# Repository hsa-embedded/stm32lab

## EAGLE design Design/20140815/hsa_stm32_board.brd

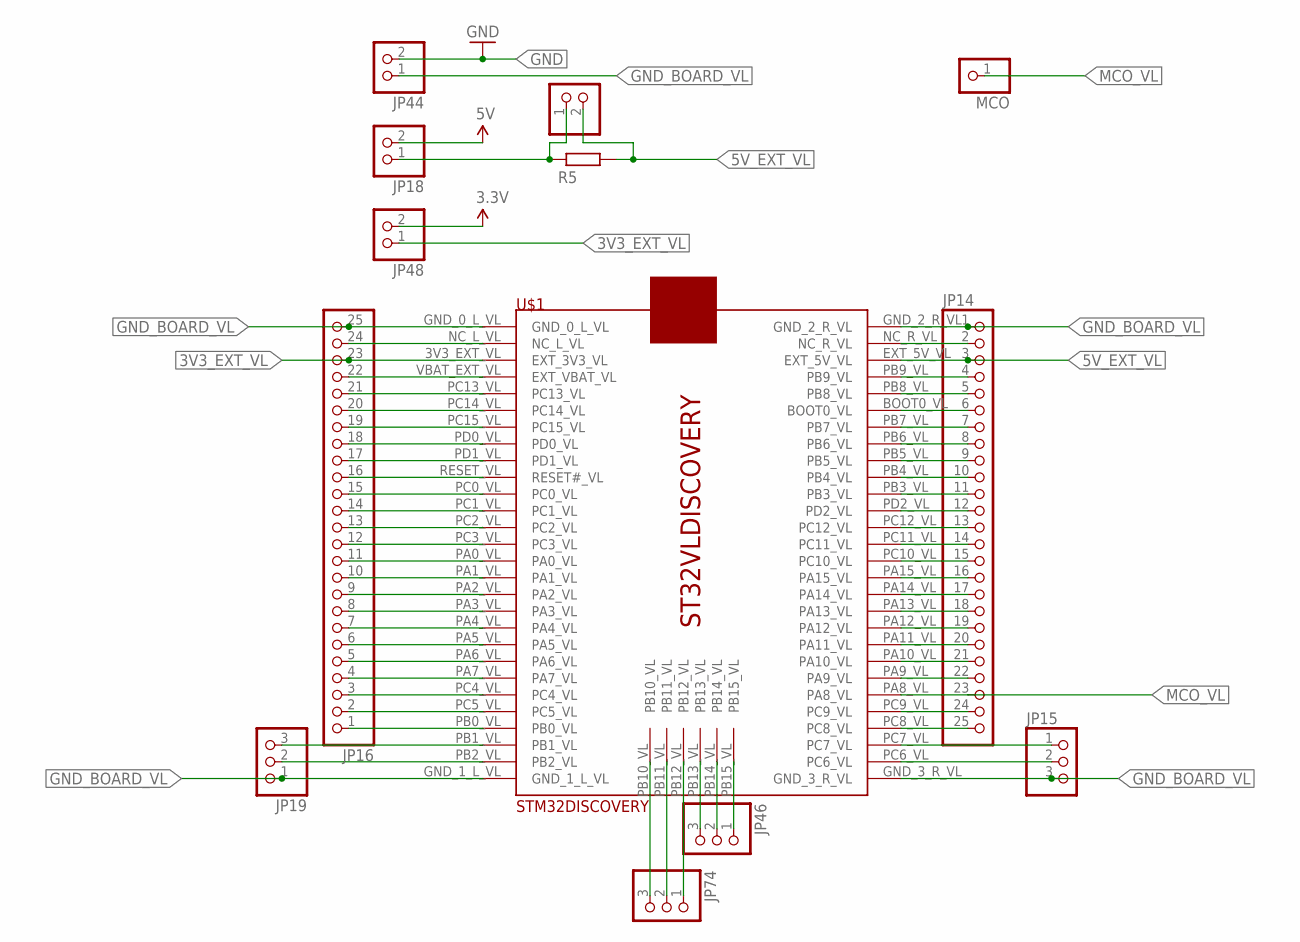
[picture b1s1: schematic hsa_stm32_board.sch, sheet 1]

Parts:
JP14, JP16: PINHD-1X25; 1X25
JP15, JP19, JP46, JP74: PINHD-1X3; 1X03
JP18, JP44, JP48, JP75: PINHD-1X2/90; 1X02/90
MCO: PINHD-1X1; 1X01
R5: R-EU_0207/10; 0207/10
U$1: STM32DISCOVERY

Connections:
3.3V: JP48.2; also elsewhere on the board
3V3_EXT_VL: JP16.23, JP48.1, U$1.3V3_EXT_VL (EXT_3V3_VL)
5V: JP18.2; also elsewhere on the board
5V_EXT_VL: JP14.3, JP75.2, R5.2, U$1.EXT_5V_VL
GND: JP44.2; also elsewhere on the board
GND_BOARD_VL: JP14.1, JP15.3, JP16.25, JP19.1, JP44.1, U$1.GND_0_L_VL, U$1.GND_1_L_VL, U$1.GND_2_R_VL, U$1.GND_3_R_VL
MCO_VL: JP14.23, MCO.1, U$1.PA8_VL
unnamed: JP18.1, JP75.1, R5.1
unnamed: JP14.2, U$1.NC_R_VL
unnamed: JP14.4, U$1.PB9_VL
unnamed: JP14.5, U$1.PB8_VL
unnamed: JP14.6, U$1.BOOT0_VL
unnamed: JP14.7, U$1.PB7_VL
unnamed: JP14.8, U$1.PB6_VL
unnamed: JP14.9, U$1.PB5_VL
unnamed: JP14.10, U$1.PB4_VL
unnamed: JP14.11, U$1.PB3_VL
unnamed: JP14.12, U$1.PD2_VL
unnamed: JP14.13, U$1.PC12_VL
unnamed: JP14.14, U$1.PC11_VL
unnamed: JP14.15, U$1.PC10_VL
unnamed: JP14.16, U$1.PA15_VL
unnamed: JP14.17, U$1.PA14_VL
unnamed: JP14.18, U$1.PA13_VL
unnamed: JP14.19, U$1.PA12_VL
unnamed: JP14.20, U$1.PA11_VL
unnamed: JP14.21, U$1.PA10_VL
unnamed: JP14.22, U$1.PA9_VL
unnamed: JP14.24, U$1.PC9_VL
unnamed: JP14.25, U$1.PC8_VL
unnamed: JP15.1, U$1.PC7_VL
unnamed: JP15.2, U$1.PC6_VL
unnamed: JP16.1, U$1.PB0_VL
unnamed: JP16.2, U$1.PC5_VL
unnamed: JP16.3, U$1.PC4_VL
unnamed: JP16.4, U$1.PA7_VL
unnamed: JP16.5, U$1.PA6_VL
unnamed: JP16.6, U$1.PA5_VL
unnamed: JP16.7, U$1.PA4_VL
unnamed: JP16.8, U$1.PA3_VL
unnamed: JP16.9, U$1.PA2_VL
unnamed: JP16.10, U$1.PA1_VL
unnamed: JP16.11, U$1.PA0_VL
unnamed: JP16.12, U$1.PC3_VL
unnamed: JP16.13, U$1.PC2_VL
unnamed: JP16.14, U$1.PC1_VL
unnamed: JP16.15, U$1.PC0_VL
unnamed: JP16.16, U$1.RESET_VL (RESET#_VL)
unnamed: JP16.17, U$1.PD1_VL
unnamed: JP16.18, U$1.PD0_VL
unnamed: JP16.19, U$1.PC15_VL
unnamed: JP16.20, U$1.PC14_VL
unnamed: JP16.21, U$1.PC13_VL
unnamed: JP16.22, U$1.VBAT_EXT_VL (EXT_VBAT_VL)
unnamed: JP16.24, U$1.NC_L_VL
unnamed: JP19.2, U$1.PB2_VL
unnamed: JP19.3, U$1.PB1_VL
unnamed: JP46.1, U$1.PB15_VL
unnamed: JP46.2, U$1.PB14_VL
unnamed: JP46.3, U$1.PB13_VL
unnamed: JP74.1, U$1.PB12_VL
unnamed: JP74.2, U$1.PB11_VL
unnamed: JP74.3, U$1.PB10_VL

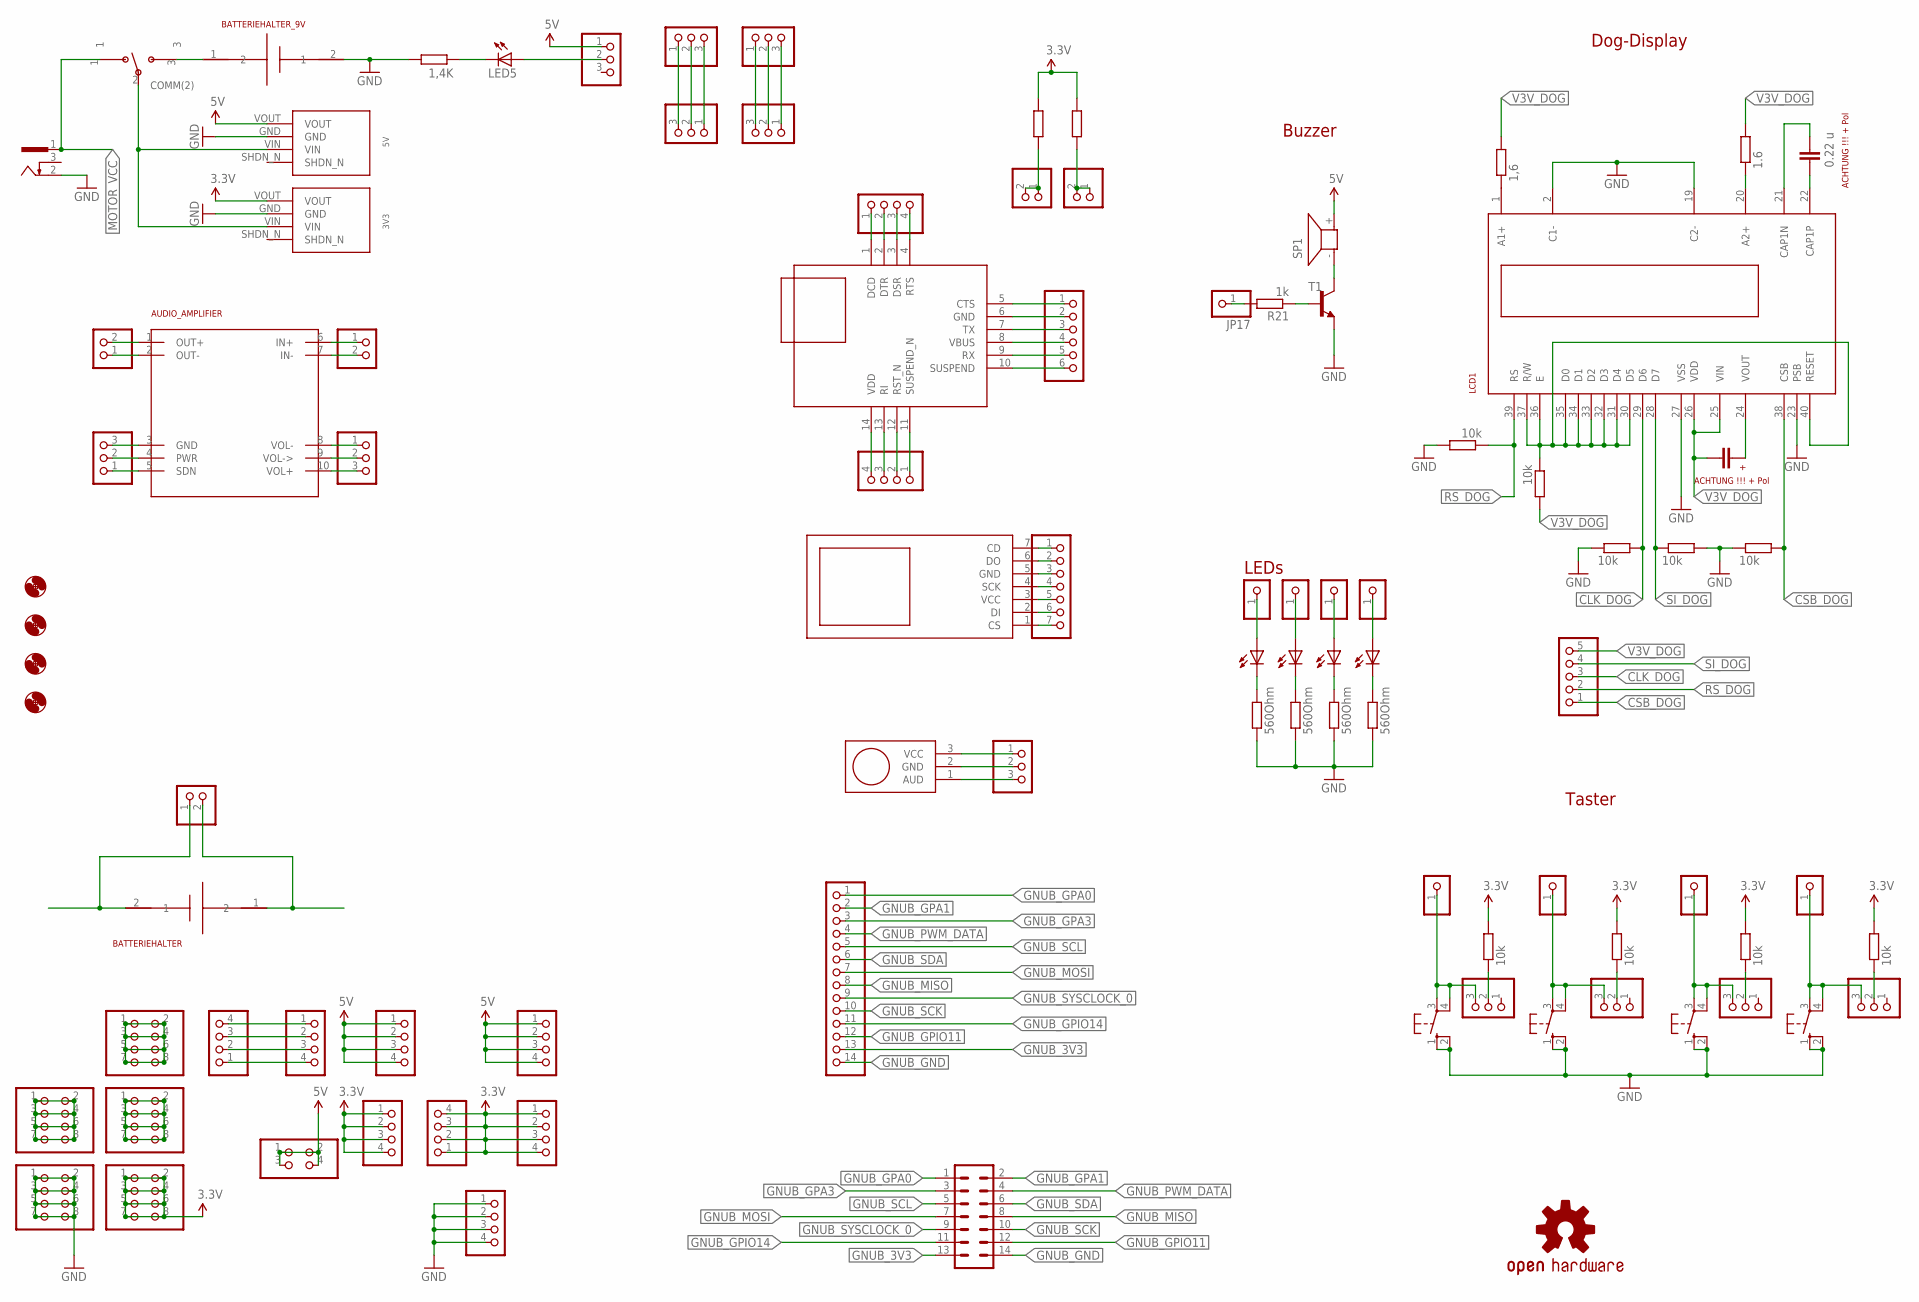
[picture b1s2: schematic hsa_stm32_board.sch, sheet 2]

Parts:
3V3, 5V: VOLTAGE_REGULATOR; VOL_REG
C2: 0.22 u; C025-040X050
C3: 1 u; C025-040X050
H1, H2, H3, H4: MOUNT-HOLE2.8; 2,8
JP1: PINHD-1X5; 1X05
JP4, JP30, JP33, JP34, JP50, JP52, JP59, JP60, JP61, JP62: PINHD-1X3; 1X03
JP5, JP6, JP7, JP8, JP9, JP10, JP11, JP12, JP17: PINHD-1X1; 1X01
JP24, JP28, JP29, JP36, JP37, JP40, JP41, JP42, JP47: PINHD-1X4; 1X04
JP27: PINHD-1X4/90; 1X04/90
JP31, JP32, JP43, JP65, JP66: PINHD-1X2; 1X02
JP38: PINHD-1X6; 1X06
JP39: PINHD-1X7; 1X07
JP45, JP67, JP68, JP69, JP70: PINHD-2X4; 2X04
JP49, JP51: PINHD-1X3/90; 1X03/90
JP64: PINHD-1X14; 1X14
JP71: PINHD-2X2; 2X02
LCD1: ZEITERFASSUNG_-OPTO_DOGM
LED1, LED2, LED3, LED4, LED5: LED5MM
LOGO1: OSHW-LOGOL; OSHW-LOGO-L
R1, R2, R3, R4: 560Ohm; 0207/10
R6: 1,4K; 0207/10
R7: 1.6; 0207/10
R8: 1,6; 0207/10
R9, R10, R11, R12, R13, R14, R15, R16, R17: 10k; 0207/10
R21: 1k; 0207/10
R22, R23: R-EU_0207/10; 0207/10
S1, S2, S3, S4: CPU-K_MODULE_REV3.0_SWITCH-OMRON_10-XX; CPU-K_MODULE_REV3.0_SWITCH-OMRON_B3F-10XX
SP1: BUZZER_F/PMX04; BUZZER_F/PMX04A
SV3: ML14
T1: TRANSISTOR_BC337; TRANSISTOR_TO92
U$2: USB_TO_SERIAL_ADAPTER; USB_TO_SERIAL
U$4: KIPPSCHALTER(EIN,AUS,EIN); KIPPSCHALTER
U$5: MIC
U$6: BATTERIEHALTER; BH_KZH_20
U$7: BATTERIEHALTER_9V
U$9: AUDIO_AMPLIFIER
U$12: MICRO_SD_HALTER; MIKRO_SD_HALTER
X1: 733980-62

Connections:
3.3V: 3V3.VOUT, JP29.1, JP29.2, JP29.3, JP29.4, JP41.1, JP41.2, JP41.3, JP41.4, JP47.1, JP47.2, JP47.3, JP47.4, JP70.1, JP70.2, JP70.3, JP70.4, JP70.5, JP70.6, JP70.7, JP70.8, R14.2, R15.2, R16.2, R17.2, R22.2, R23.2; also elsewhere on the board
5V: 5V.VOUT, JP4.1, JP28.1, JP28.2, JP28.3, JP28.4, JP40.1, JP40.2, JP40.3, JP40.4, JP71.1, JP71.2, JP71.3, JP71.4, SP1.+ (2); also elsewhere on the board
CLK_DOG: JP1.3, LCD1.29 (D6), R11.2
CSB_DOG: JP1.1, LCD1.38 (CSB), R13.2
GND: 3V3.GND, 5V.GND, JP42.1, JP42.2, JP42.3, JP42.4, JP67.1, JP67.2, JP67.3, JP67.4, JP67.5, JP67.6, JP67.7, JP67.8, LCD1.2 (C1-), LCD1.19 (C2-), LCD1.23 (PSB), LCD1.27 (VSS), R1.1, R2.1, R3.1, R4.1, R6.2, R9.2, R11.1, R12.2, R13.1, S1.1 (S), S1.2 (S1), S2.1 (S), S2.2 (S1), S3.1 (S), S3.2 (S1), S4.1 (S), S4.2 (S1), T1.1 (E), U$7.2 (1), X1.2; also elsewhere on the board
GNUB_3V3: JP64.13, SV3.13
GNUB_GND: JP64.14, SV3.14
GNUB_GPA0: JP64.1, SV3.1
GNUB_GPA1: JP64.2, SV3.2
GNUB_GPA3: JP64.3, SV3.3
GNUB_GPIO11: JP64.12, SV3.12
GNUB_GPIO14: JP64.11, SV3.11
GNUB_MISO: JP64.8, SV3.8
GNUB_MOSI: JP64.7, SV3.7
GNUB_PWM_DATA: JP64.4, SV3.4
GNUB_SCK: JP64.10, SV3.10
GNUB_SCL: JP64.5, SV3.5
GNUB_SDA: JP64.6, SV3.6
GNUB_SYSCLOCK_0: JP64.9, SV3.9
MOTOR_VCC: U$4.1, X1.1; also elsewhere on the board
unnamed: C2.2, LCD1.22 (CAP1P)
unnamed: C2.1, LCD1.21 (CAP1N)
unnamed: LCD1.20 (A2+), R7.1
unnamed: LCD1.30 (D5), LCD1.31 (D4), LCD1.32 (D3), LCD1.33 (D2), LCD1.34 (D1), LCD1.35 (D0), LCD1.36 (E), LCD1.37 (R/W), LCD1.40 (RESET), R10.1
unnamed: LCD1.1 (A1+), R8.1
unnamed: C3.2, LCD1.24 (VOUT)
unnamed: LED4.K (C), R4.2
unnamed: LED3.K (C), R3.2
unnamed: LED2.K (C), R2.2
unnamed: LED1.K (C), R1.2
unnamed: JP6.1, LED2.A
unnamed: JP7.1, LED3.A
unnamed: JP8.1, LED4.A
unnamed: 3V3.VIN, 5V.VIN, U$4.2 (COMM(2))
unnamed: JP62.2, R14.1
unnamed: JP61.2, R15.1
unnamed: JP9.1, JP62.3, S1.3, S1.4 (P1)
unnamed: JP10.1, JP61.3, S2.3, S2.4 (P1)
unnamed: JP60.2, R16.1
unnamed: JP59.2, R17.1
unnamed: JP11.1, JP60.3, S3.3, S3.4 (P1)
unnamed: JP12.1, JP59.3, S4.3, S4.4 (P1)
unnamed: U$4.3, U$7.1 (2)
unnamed: LED5.K (C), R6.1
unnamed: JP4.2, LED5.A
unnamed: JP5.1, LED1.A
unnamed: SP1.- (1), T1.3 (C)
unnamed: JP43.1, U$6.2 (1)
unnamed: JP17.1, R21.2
unnamed: JP43.2, U$6.1 (2)
unnamed: JP24.4, JP27.1
unnamed: JP24.3, JP27.2
unnamed: JP24.2, JP27.3
unnamed: JP24.1, JP27.4
unnamed: JP32.2, U$9.1 (OUT+)
unnamed: JP32.1, U$9.2 (OUT-)
unnamed: JP31.1, U$9.6 (IN+)
unnamed: JP31.2, U$9.7 (IN-)
unnamed: JP34.1, U$9.8 (VOL-)
unnamed: JP49.3, JP50.1
unnamed: JP49.2, JP50.2
unnamed: JP49.1, JP50.3
unnamed: JP30.1, U$5.3 (VCC)
unnamed: JP30.2, U$5.2 (GND)
unnamed: JP30.3, U$5.1 (AUD)
unnamed: JP34.2, U$9.9 (VOL->)
unnamed: JP34.3, U$9.10 (VOL+)
unnamed: JP33.3, U$9.3 (GND)
unnamed: JP33.2, U$9.4 (PWR)
unnamed: JP33.1, U$9.5 (SDN)
unnamed: JP36.1, U$2.1 (DCD)
unnamed: JP36.2, U$2.2 (DTR)
unnamed: JP36.3, U$2.3 (DSR)
unnamed: JP36.4, U$2.4 (RTS)
unnamed: JP37.1, U$2.11 (SUSPEND_N)
unnamed: JP37.2, U$2.12 (RST_N)
unnamed: JP37.3, U$2.13 (RI)
unnamed: JP37.4, U$2.14 (VDD)
unnamed: JP38.1, U$2.5 (CTS)
unnamed: JP38.2, U$2.6 (GND)
unnamed: JP38.3, U$2.7 (TX)
unnamed: JP38.4, U$2.8 (VBUS)
unnamed: JP38.5, U$2.9 (RX)
unnamed: JP38.6, U$2.10 (SUSPEND)
unnamed: JP39.1, U$12.7 (CD)
unnamed: JP39.2, U$12.6 (DO)
unnamed: JP39.3, U$12.5 (GND)
unnamed: JP39.4, U$12.4 (SCK)
unnamed: JP39.5, U$12.3 (VCC)
unnamed: JP39.6, U$12.2 (DI)
unnamed: JP39.7, U$12.1 (CS)
unnamed: JP51.3, JP52.1
unnamed: JP51.2, JP52.2
unnamed: JP51.1, JP52.3
unnamed: R21.1, T1.2 (B)
unnamed: JP65.1, JP65.2, R23.1
unnamed: JP66.1, JP66.2, R22.1
unnamed: JP45.1, JP45.2, JP45.3, JP45.4, JP45.5, JP45.6, JP45.7, JP45.8
unnamed: JP68.1, JP68.2, JP68.3, JP68.4, JP68.5, JP68.6, JP68.7, JP68.8
unnamed: JP69.1, JP69.2, JP69.3, JP69.4, JP69.5, JP69.6, JP69.7, JP69.8
RS_DOG: JP1.2, LCD1.39 (RS), R9.1
SI_DOG: JP1.4, LCD1.28 (D7), R12.1
V3V_DOG: C3.1, JP1.5, LCD1.25 (VIN), LCD1.26 (VDD), R7.2, R8.2, R10.2

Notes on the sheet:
Dog-Display
Taster
Buzzer
LEDs
ACHTUNG !!! + Pol

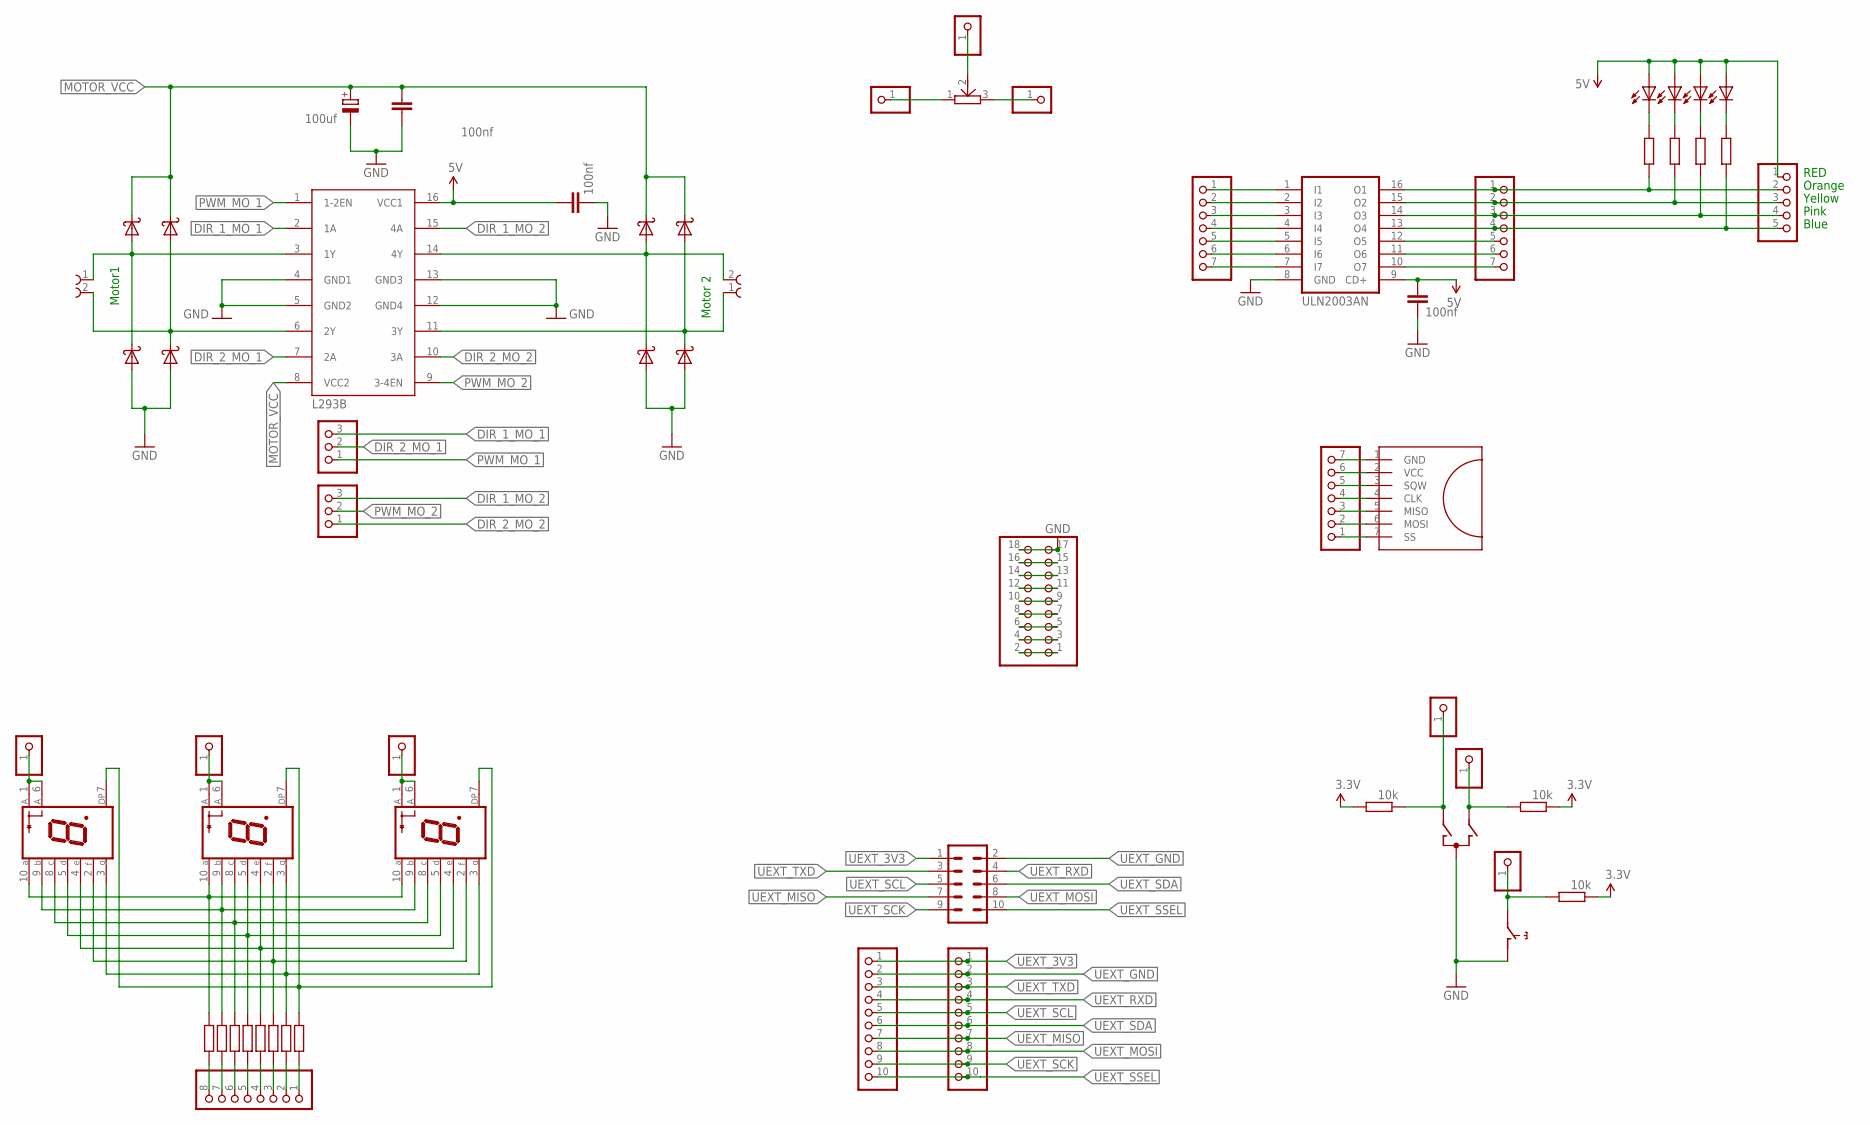
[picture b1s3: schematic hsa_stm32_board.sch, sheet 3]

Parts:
C4, C5, C6: 100nf; RCL_C025-040X050
C7: 100uf; RCL_E2,5-6
D1, D2, D3, D4, D5, D6, D7, D8: 1N5819; DO41-10
IC1: ULN2003AN; DIL16
IC2: L293D; DIL16
JP2, JP3, JP13, JP23, JP53, JP54, JP55, JP72, JP73: PINHD-1X1; 1X01
JP20, JP63: PINHD-1X10; 1X10
JP21, JP26, JP35: PINHD-1X7; 1X07
JP22: PINHD-1X8; 1X08
JP25: PINHD-1X5/90; 1X05/90
JP56: PINHD-2X9; 2X09
JP57, JP58: PINHD-1X3; 1X03
K1, K2: 691210910002
LED6, LED7, LED8: LA-401MD; LA-401
LED9, LED10, LED11, LED12: LED3MM
R18, R19, R20: 10k; 0207/10
R24, R25, R26, R27, R28, R29, R30, R31, R32, R33, R34, R35: R-EU_0207/10; 0207/10
SV2: CON-HARTING-ML_ML10
SW1: EC12E_SW; ALPS_EC12E_SW
U$10: RTC
U$17: THUMBWHEEL_POTI

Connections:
3.3V: R18.1, R19.2, R20.1; also elsewhere on the board
5V: C4.1, C6.1, IC1.9 (CD+), IC2.16 (VCC1), JP25.1, LED9.A, LED10.A, LED11.A, LED12.A; also elsewhere on the board
DIR_1_MO_1: IC2.2 (1A), JP57.3
DIR_1_MO_2: IC2.15 (4A), JP58.3
DIR_2_MO_1: IC2.7 (2A), JP57.2
DIR_2_MO_2: IC2.10 (3A), JP58.1
GND: C4.2, C5.2, C6.2, C7.-, D3.A, D4.A, D7.A, D8.A, IC1.8 (GND), IC2.4 (GND1), IC2.5 (GND2), IC2.12 (GND4), IC2.13 (GND3), JP56.17, JP56.18, SW1.C, SW1.D (1); also elsewhere on the board
MOTOR_VCC: C5.1, C7.+, D1.C, D2.C, D5.C, D6.C, IC2.8 (VCC2); also elsewhere on the board
unnamed: JP2.1, R19.1, SW1.A
unnamed: LED9.K (C), R32.2
unnamed: LED10.K (C), R34.2
unnamed: JP3.1, R18.2, SW1.B
unnamed: JP13.1, R20.2, SW1.E (2)
unnamed: D2.A, D4.C, IC2.14 (4Y), K1.2
unnamed: IC1.12 (O5), JP21.5
unnamed: IC1.11 (O6), JP21.6
unnamed: IC1.10 (O7), JP21.7
unnamed: IC1.5 (I5), JP26.5
unnamed: IC1.16 (O1), JP21.1, JP25.2, R32.1
unnamed: IC1.15 (O2), JP21.2, JP25.3, R34.1
unnamed: IC1.6 (I6), JP26.6
unnamed: IC1.7 (I7), JP26.7
unnamed: JP56.1, JP56.2
unnamed: JP56.3, JP56.4
unnamed: IC1.14 (O3), JP21.3, JP25.4, R33.1
unnamed: IC1.13 (O4), JP21.4, JP25.5, R35.1
unnamed: JP56.5, JP56.6
unnamed: IC1.4 (I4), JP26.4
unnamed: IC1.3 (I3), JP26.3
unnamed: IC1.2 (I2), JP26.2
unnamed: IC1.1 (I1), JP26.1
unnamed: JP56.7, JP56.8
unnamed: JP56.9, JP56.10
unnamed: JP56.11, JP56.12
unnamed: JP35.1, U$10.7 (SS)
unnamed: JP35.2, U$10.6 (MOSI)
unnamed: JP35.3, U$10.5 (MISO)
unnamed: JP35.4, U$10.4 (CLK)
unnamed: JP35.5, U$10.3 (SQW)
unnamed: JP35.6, U$10.2 (VCC)
unnamed: JP35.7, U$10.1 (GND)
unnamed: D1.A, D3.C, IC2.11 (3Y), K1.1
unnamed: JP55.1, U$17.1 (A)
unnamed: JP54.1, U$17.2 (W)
unnamed: D6.A, D8.C, IC2.3 (1Y), K2.1
unnamed: D5.A, D7.C, IC2.6 (2Y), K2.2
unnamed: JP53.1, U$17.3 (B)
unnamed: LED12.K (C), R35.2
unnamed: LED11.K (C), R33.2
unnamed: JP56.13, JP56.14
unnamed: JP56.15, JP56.16
unnamed: JP22.8, R24.1
unnamed: LED6.9 (B), LED7.9 (B), LED8.9 (B), R25.2
unnamed: LED6.8 (C), LED7.8 (C), LED8.8 (C), R26.2
unnamed: LED6.5 (D), LED7.5 (D), LED8.5 (D), R27.2
unnamed: LED6.4 (E), LED7.4 (E), LED8.4 (E), R28.2
unnamed: LED6.2 (F), LED7.2 (F), LED8.2 (F), R29.2
unnamed: LED6.3 (G), LED7.3 (G), LED8.3 (G), R30.2
unnamed: LED6.7 (DP), LED7.7 (DP), LED8.7 (DP), R31.2
unnamed: LED6.10 (A), LED7.10 (A), LED8.10 (A), R24.2
unnamed: JP22.7, R25.1
unnamed: JP22.6, R26.1
unnamed: JP22.5, R27.1
unnamed: JP22.4, R28.1
unnamed: JP22.3, R29.1
unnamed: JP22.2, R30.1
unnamed: JP22.1, R31.1
unnamed: JP72.1, LED6.1 (A), LED6.6 (A)
unnamed: JP73.1, LED7.1 (A), LED7.6 (A)
unnamed: JP23.1, LED8.1 (A), LED8.6 (A)
PWM_MO_1: IC2.1 (1-2EN), JP57.1
PWM_MO_2: IC2.9 (3-4EN), JP58.2
UEXT_3V3: JP20.1, JP63.1, SV2.1
UEXT_GND: JP20.2, JP63.2, SV2.2
UEXT_MISO: JP20.7, JP63.7, SV2.7
UEXT_MOSI: JP20.8, JP63.8, SV2.8
UEXT_RXD: JP20.4, JP63.4, SV2.4
UEXT_SCK: JP20.9, JP63.9, SV2.9
UEXT_SCL: JP20.5, JP63.5, SV2.5
UEXT_SDA: JP20.6, JP63.6, SV2.6
UEXT_SSEL: JP20.10, JP63.10, SV2.10
UEXT_TXD: JP20.3, JP63.3, SV2.3

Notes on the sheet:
L293B
Motor 2
Motor1
RED
Orange
Yellow
Pink
Blue

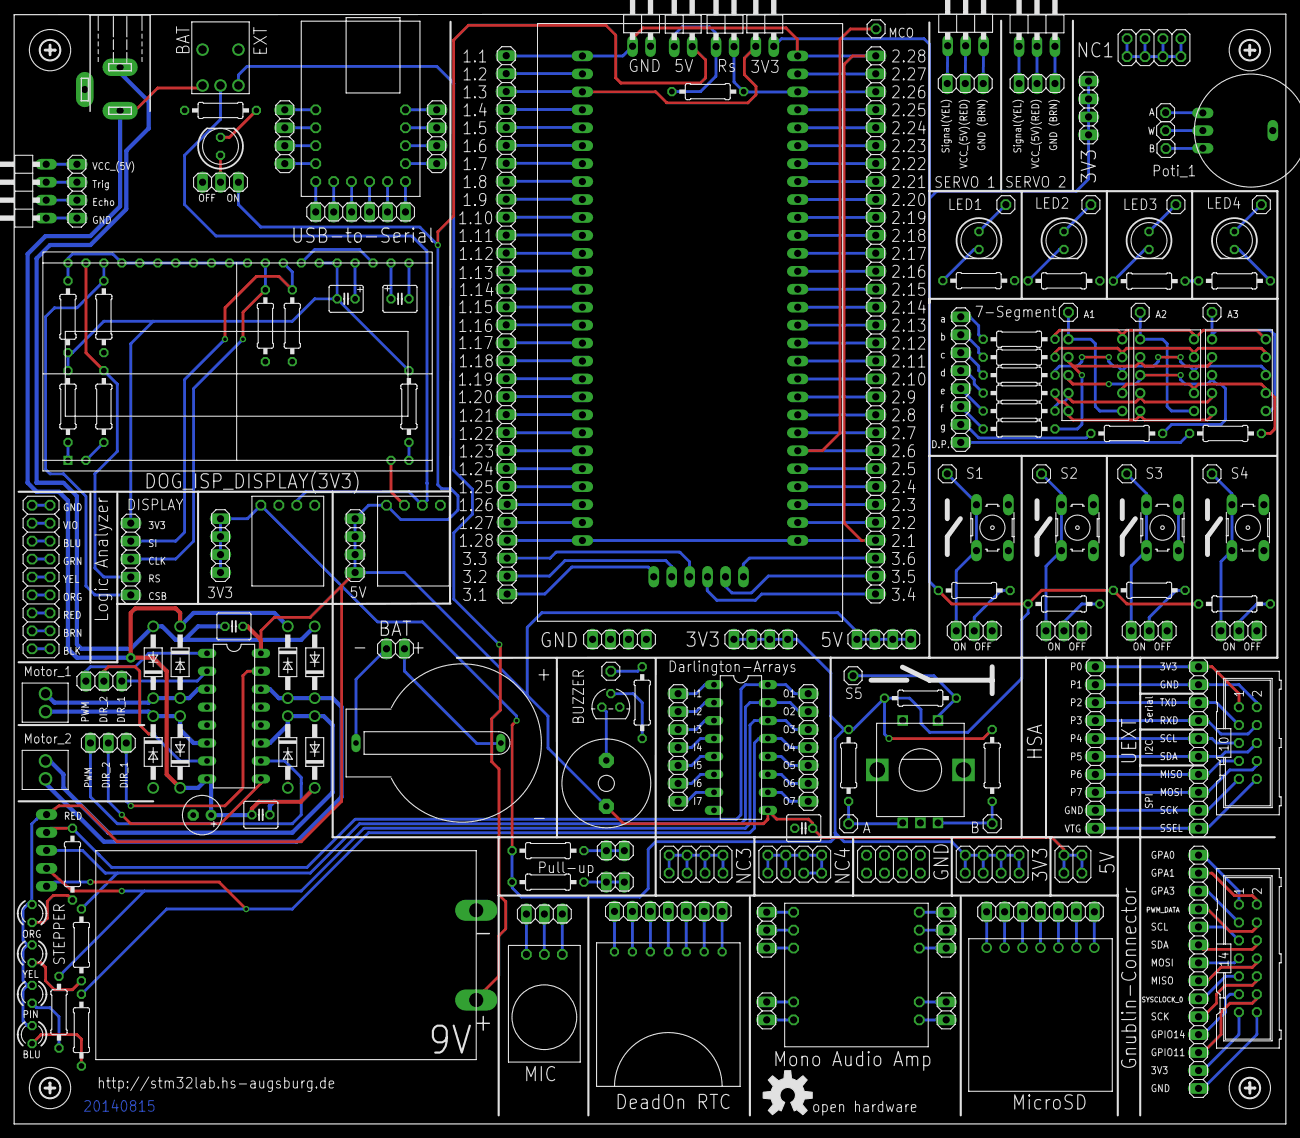
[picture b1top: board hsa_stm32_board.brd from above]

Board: 2 copper layers, 180.0 x 157.1 mm, 169 parts (1 on the bottom side), 241 nets.

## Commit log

2014-09-28 new file: .gitignore
2014-10-14 First stm32lab commit
2014-10-14 template example
2014-10-29 modified: Makefile modified: startupcode.c
2015-01-18 authors
2015-01-18 deleted authors
2015-01-22 deleted: LICENSE
2015-01-27 new file: anschluss.rst
2015-01-27 modified: anschluss.rst

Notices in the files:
parts and their libraries:
SparkFun-Aesthetics: Licensing: CC v3.0 Share-Alike You are welcome to use this library for commercial purposes.
Wuerth_Elektronik_eiCan_14_Terminal_Bloc: Copyright: Würth Elektronik
